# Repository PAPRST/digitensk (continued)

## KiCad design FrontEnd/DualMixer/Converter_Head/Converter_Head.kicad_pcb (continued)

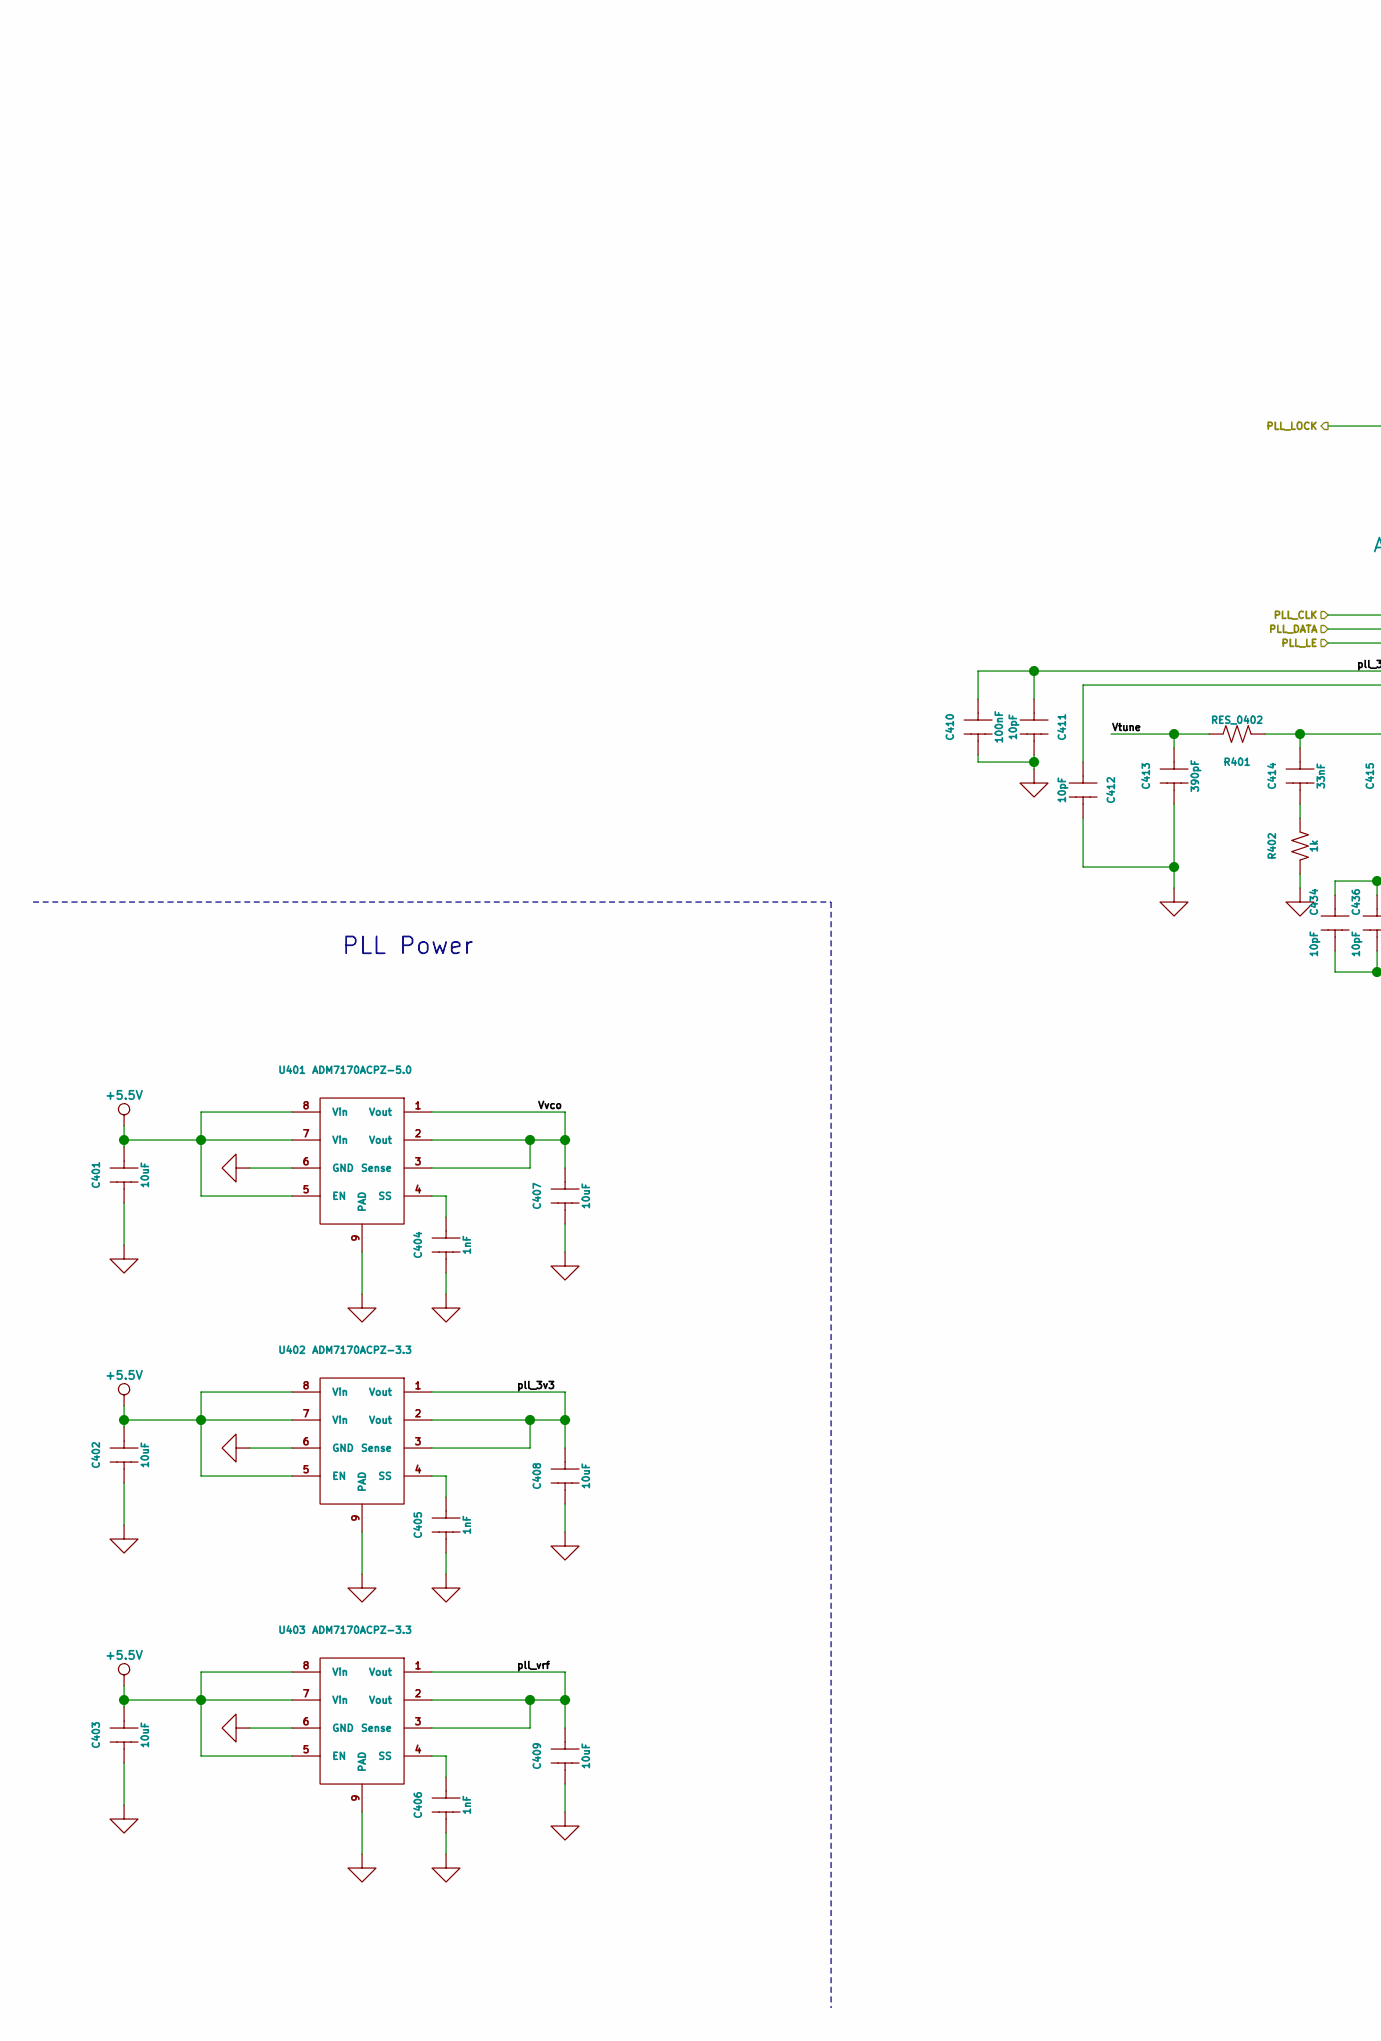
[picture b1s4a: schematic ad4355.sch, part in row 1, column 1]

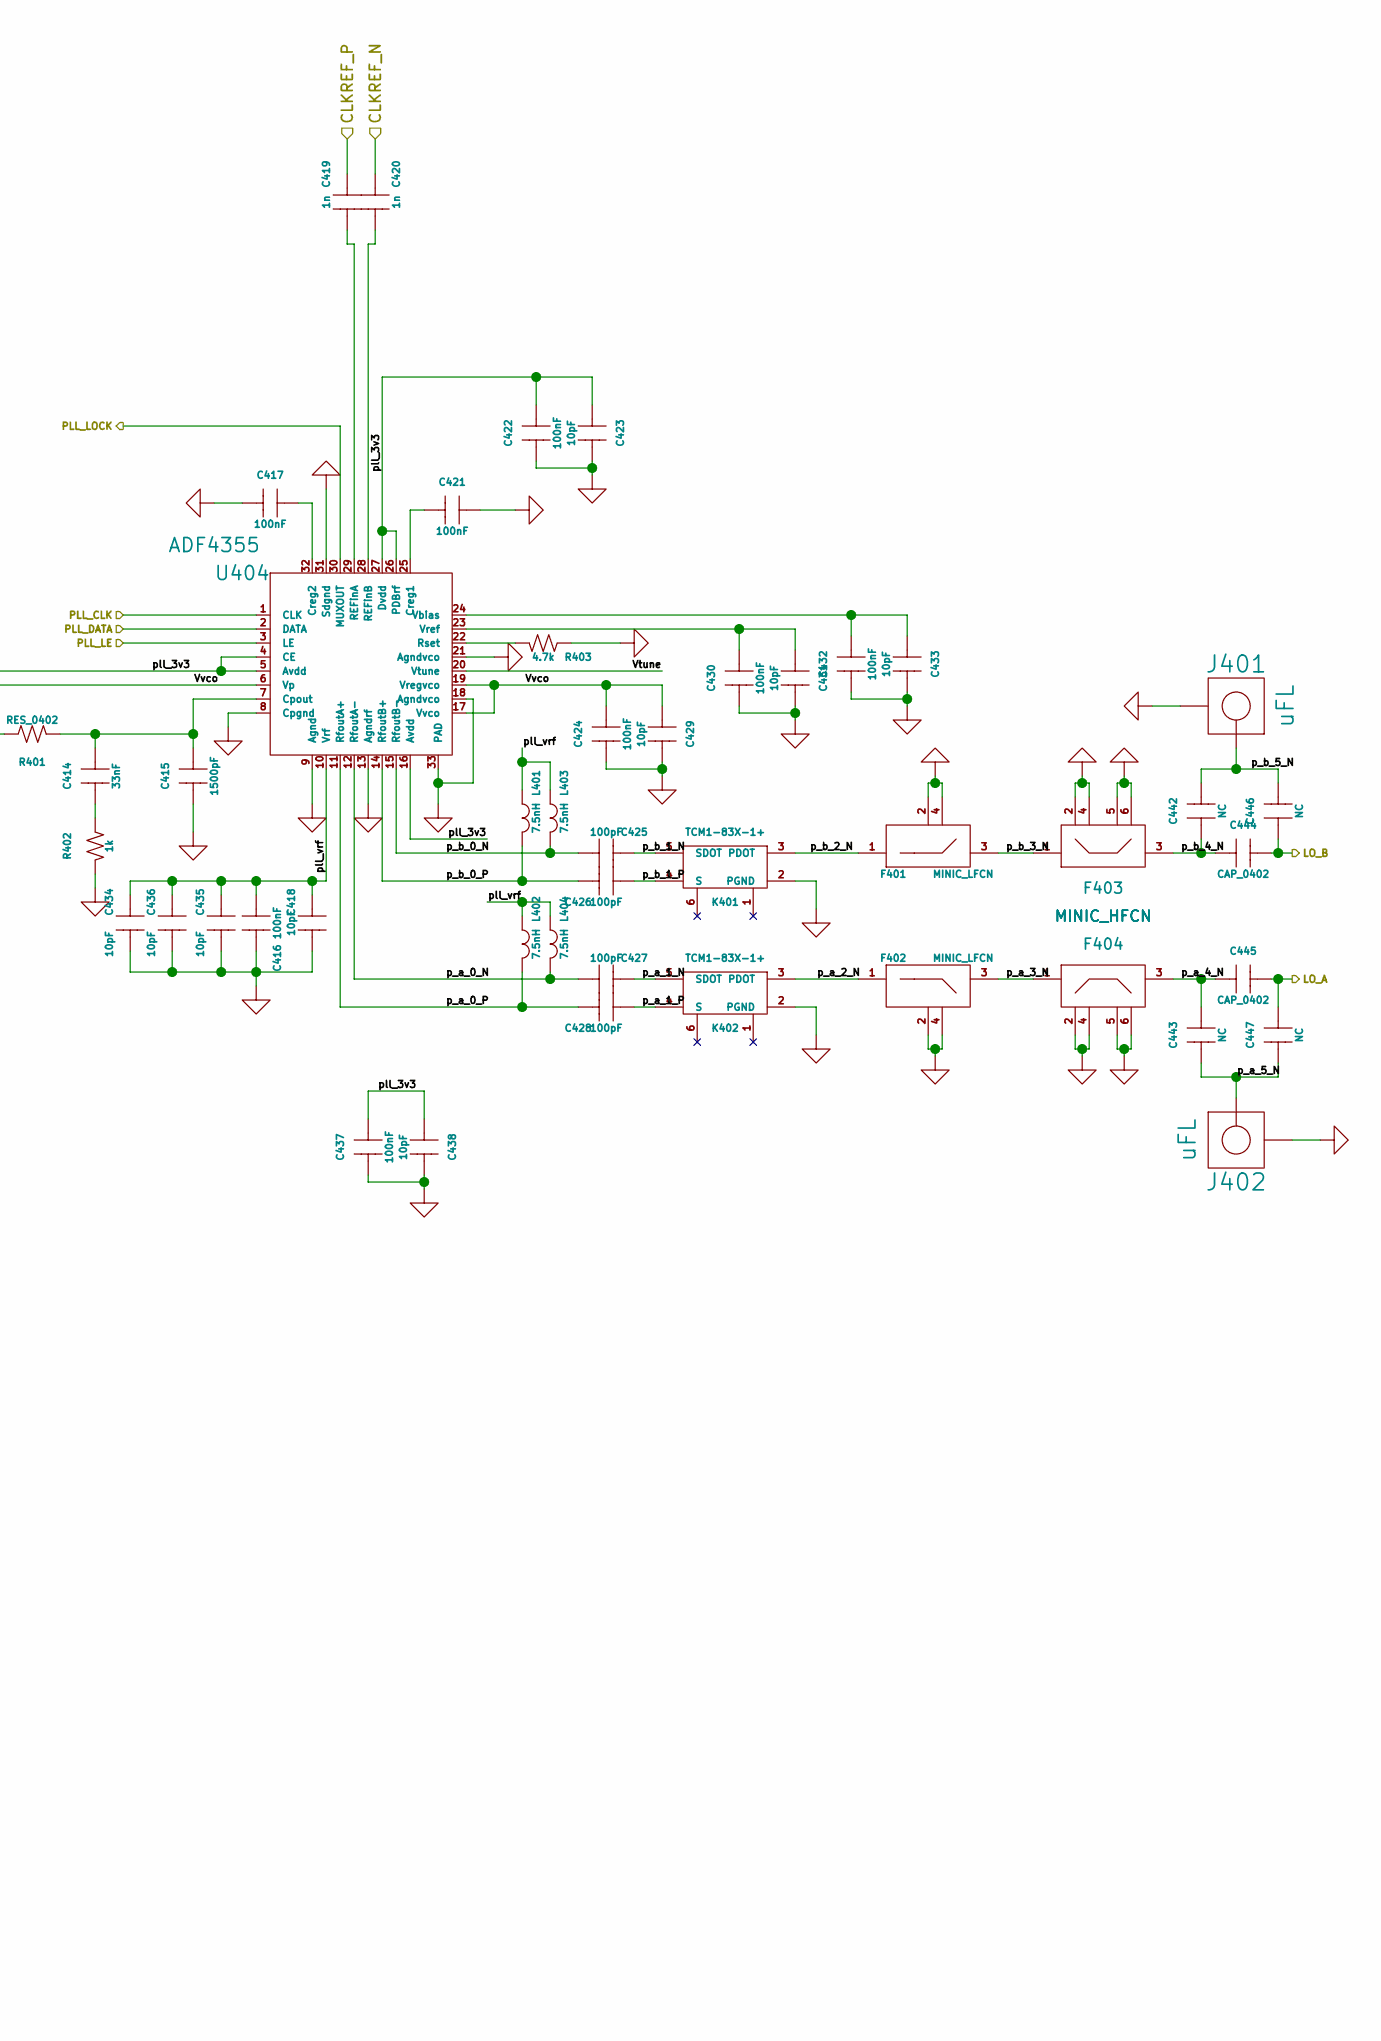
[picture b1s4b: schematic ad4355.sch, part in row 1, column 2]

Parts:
C401, C402, C403, C407, C408, C409: 10uF; SM0805
C404, C405, C406: 1nF; SM0603
C410, C416, C417, C421, C422, C424, C430, C432, C437: 100nF; SM0402
C411, C412, C418, C423, C429, C431, C433, C434, C435, C436, C438: 10pF; SM0402
C413: 390pF; SM0402
C414: 33nF; SM0402
C415: 1500pF; SM0402
C419, C420: 1n; SM0402
C425, C426, C427, C428: 100pF; SM0402
C442, C443, C446, C447: NC; SM0402
C444, C445: CAP_0402; SM0402
F401, F402: MINIC_LFCN; FV1206
F403, F404: MINIC_HFCN; FV1206
J401, J402: uFL; U.FL-R-SMT-1
K401, K402: TCM1-83X-1+; DB1627
L401, L402, L403, L404: 7.5nH; SM0402
R401: RES_0402; SM0402
R402: 1k; SM0402
R403: 4.7k; SM0402
U401: ADM7170ACPZ-5.0; DFN8_3x3mm
U402, U403: ADM7170ACPZ-3.3; DFN8_3x3mm
U404: ADF4355; QFN32_5x5mm_3.6mm

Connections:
+5.5V: C401.1, C402.1, C403.1, U401.5 (EN), U401.7 (Vin), U401.8 (Vin), U402.5 (EN), U402.7 (Vin), U402.8 (Vin), U403.5 (EN), U403.7 (Vin), U403.8 (Vin); also elsewhere on the board
/ADF4355 PLL/CLKREF_N: C420.1; also elsewhere on the board
/ADF4355 PLL/CLKREF_P: C419.1; also elsewhere on the board
/ADF4355 PLL/LO_A: C445.2, C447.1; also elsewhere on the board
/ADF4355 PLL/LO_B: C444.2, C446.1; also elsewhere on the board
/ADF4355 PLL/Vtune: C413.1, R401.1, U404.20 (Vtune)
/ADF4355 PLL/Vvco: C407.1, C412.1, C424.1, C429.1, U401.1 (Vout), U401.2 (Vout), U401.3 (Sense), U404.6 (Vp), U404.17 (Vvco), U404.19 (Vregvco)
/ADF4355 PLL/p_a_0_N: C427.1, L404.2, U404.12 (RfoutA-)
/ADF4355 PLL/p_a_0_P: C428.2, L402.2, U404.11 (RfoutA+)
/ADF4355 PLL/p_a_1_N: C427.2, K402.5 (SDOT)
/ADF4355 PLL/p_a_1_P: C428.1, K402.4 (S)
/ADF4355 PLL/p_a_2_N: F402.1 (RFIN), K402.3 (PDOT)
/ADF4355 PLL/p_a_3_N: F402.3 (RFOUT), F404.1 (RFIN)
/ADF4355 PLL/p_a_4_N: C443.1, C445.1, F404.3 (RFOUT)
/ADF4355 PLL/p_a_5_N: C443.2, C447.2, J402.1 (RF)
/ADF4355 PLL/p_b_0_N: C425.1, L403.2, U404.15 (RfoutB-)
/ADF4355 PLL/p_b_0_P: C426.2, L401.2, U404.14 (RfoutB+)
/ADF4355 PLL/p_b_1_N: C425.2, K401.5 (SDOT)
/ADF4355 PLL/p_b_1_P: C426.1, K401.4 (S)
/ADF4355 PLL/p_b_2_N: F401.1 (RFIN), K401.3 (PDOT)
/ADF4355 PLL/p_b_3_N: F401.3 (RFOUT), F403.1 (RFIN)
/ADF4355 PLL/p_b_4_N: C442.1, C444.1, F403.3 (RFOUT)
/ADF4355 PLL/p_b_5_N: C442.2, C446.2, J401.1 (RF)
/ADF4355 PLL/pll_3v3: C408.1, C410.1, C411.1, C422.1, C423.1, C437.1, C438.1, U402.1 (Vout), U402.2 (Vout), U402.3 (Sense), U404.4 (CE), U404.5 (Avdd), U404.16 (Avdd), U404.26 (PDBrf), U404.27 (Dvdd)
/ADF4355 PLL/pll_vrf: C409.1, C416.1, C418.1, C434.1, C435.1, C436.1, L401.1, L402.1, L403.1, L404.1, U403.1 (Vout), U403.2 (Vout), U403.3 (Sense), U404.10 (Vrf)
/MOSI: U404.2 (DATA); also elsewhere on the board
/PLL_LOCK: U404.30 (MUXOUT); also elsewhere on the board
/SCK: U404.1 (CLK); also elsewhere on the board
/~PLL_CS: U404.3 (LE); also elsewhere on the board
GND: C401.2, C402.2, C403.2, C404.2, C405.2, C406.2, C407.2, C408.2, C409.2, C410.2, C411.2, C412.2, C413.2, C415.2, C416.2, C417.2, C418.2, C421.1, C422.2, C423.2, C424.2, C429.2, C430.2, C431.2, C432.2, C433.2, C434.2, C435.2, C436.2, C437.2, C438.2, F401.2 (GND), F401.4 (GND), F402.2 (GND), F402.4 (GND), F403.2 (GND), F403.4 (GND), F403.5 (GND), F403.6 (GND), F404.2 (GND), F404.4 (GND), F404.5 (GND), F404.6 (GND), J401.2 (GND), J402.2 (GND), K401.2 (PGND), K402.2 (PGND), R402.2, R403.1, U401.6 (GND), U401.9 (PAD), U402.6 (GND), U402.9 (PAD), U403.6 (GND), U403.9 (PAD), U404.8 (Cpgnd), U404.9 (Agnd), U404.13 (Agndrf), U404.18 (Agndvco), U404.21 (Agndvco), U404.31 (Sdgnd), U404.33 (PAD); also elsewhere on the board
unnamed: C404.1, U401.4 (SS)
unnamed: C405.1, U402.4 (SS)
unnamed: C406.1, U403.4 (SS)
unnamed: C414.1, C415.1, R401.2, U404.7 (Cpout)
unnamed: C414.2, R402.1
unnamed: C417.1, U404.32 (Creg2)
unnamed: C419.2, U404.29 (REFinA)
unnamed: C420.2, U404.28 (REFinB)
unnamed: C421.2, U404.25 (Creg1)
unnamed: C430.1, C431.1, U404.23 (Vref)
unnamed: C432.1, C433.1, U404.24 (Vbias)
unnamed: R403.2, U404.22 (Rset)

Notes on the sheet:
PLL Power

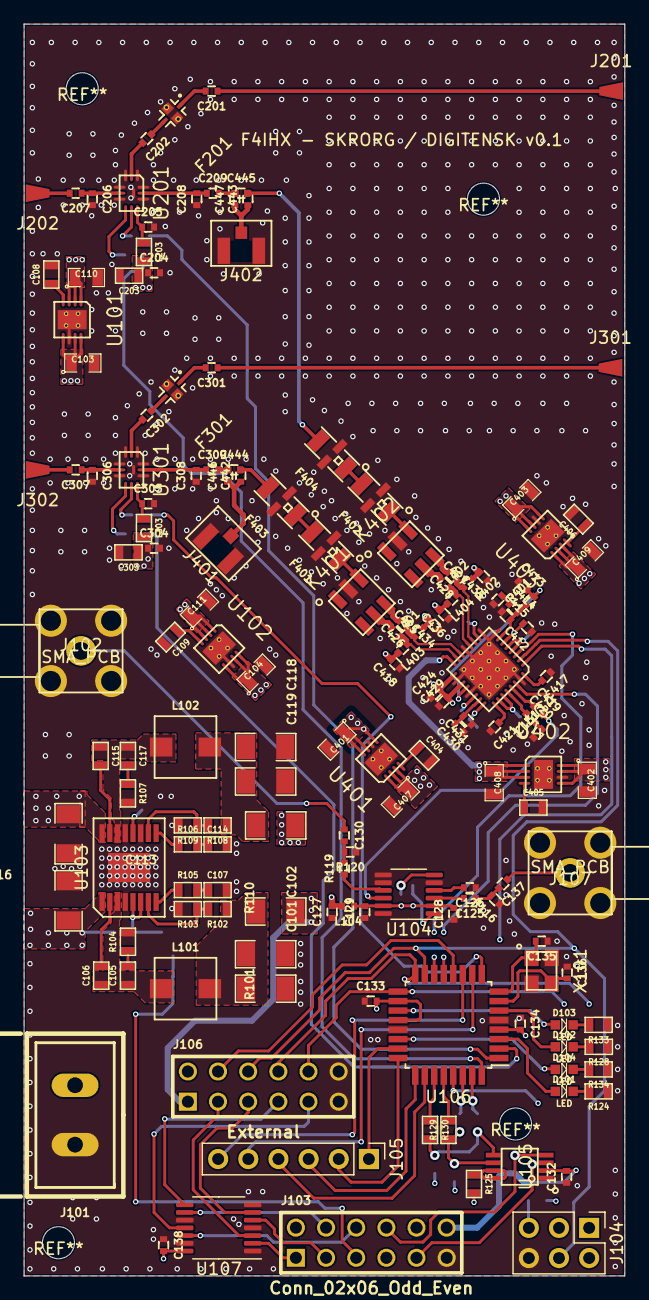
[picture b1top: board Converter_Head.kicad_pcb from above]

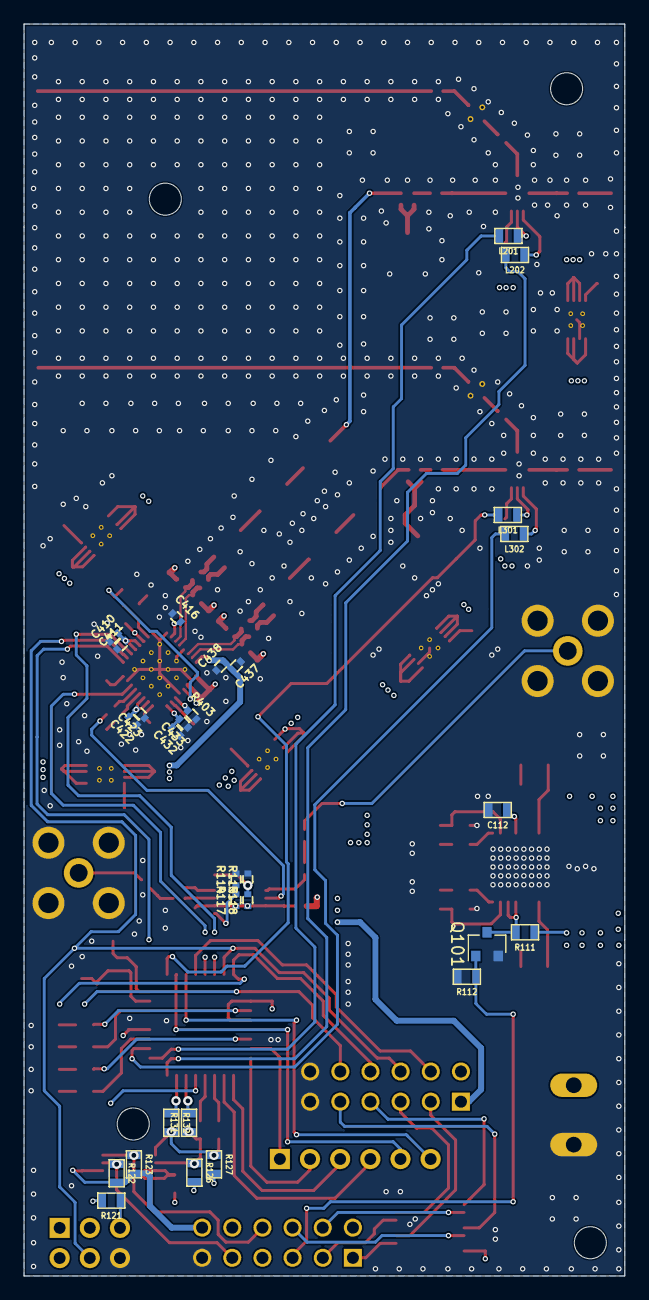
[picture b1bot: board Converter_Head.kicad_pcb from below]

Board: 4 copper layers, 50.6 x 105.5 mm, 184 parts (29 on the bottom side), 136 nets.

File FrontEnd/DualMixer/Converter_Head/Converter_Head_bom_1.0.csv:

Component,Part,References,Value,Vendor,SKU,Footprint,Quantity Per PCB,Man. Ref.,Status
1,CAP_0402,C206 C208 C306 C308,0.15pF,,,SM0402,4,,
2,CAP_0402,C125 C127 C128 C129 C130 C131 C132 C133 C134 C137 C138,0.1uF,,,SM0402,11,,
3,CAP_0603,C114,1.68n,,,SM0603,1,,
4,CAP_0603,C410 C416 C417 C421 C422 C424 C430 C432 C437,100nF,,,SM0402,9,,
5,CAP_0402,C425 C426 C427 C428,100pF,,,SM0402,4,,
6,CAP_0402,C126,10nF,,,SM0402,1,,
7,CAP_0402,C135 C136 C411 C412 C418 C423 C429 C431 C433 C434 C435 C436 C438,10pF,,,SM0402,13,,
8,CAP_1206,C101 C102 C113 C116 C118 C119,10u,,,SM1206,6,,
9,CAP_0805,C103 C104 C110 C111 C401 C402 C403 C407 C408 C409,10uF,,,SM0805,10,,
10,CAP_0402,C415,1500pF,,,SM0402,1,,
11,CAP_0402,C419 C420,1n,,,SM0402,2,,
12,CAP_0603,C108 C109 C404 C405 C406,1nF,,,SM0603,5,,
13,CAP_0603,C203 C303,1uF,,,SM0603,2,,
14,CAP_0603,C107,2.8n,,,SM0603,1,,
15,CAP_0402,C205 C207 C209 C305 C307 C309,22pF,,,SM0402,6,,
16,CAP_0402,C201 C202 C301 C302,30pF,,,SM0402,4,,
17,CAP_0402,C414,33nF,,,SM0402,1,,
18,CAP_0402,C413,390pF,,,SM0402,1,,
19,CAP_0603,C112,4.7u,,,SM0603,1,,
20,CAP_0603,C105 C117,470p,,,SM0603,2,,
21,CAP_0603,C106 C115,47n,,,SM0603,2,,
22,CAP_0402,C204 C304,47pF,,,SM0402,2,,
23,CAP_0402,C444 C445,CAP_0402,,,SM0402,2,,
24,CAP_0402,C442 C443 C446 C447,NC,,,SM0402,4,,
25,LED,D101 D102 D103 D104,LED,,,LED-0603,4,,
26,BFCW,F201 F301,BFCW-542+,,,JC0603C,2,,
27,MINIC_HFCN,F403 F404,MINIC_HFCN,,,FV1206,2,,
28,MINIC_LFCN,F401 F402,MINIC_LFCN,,,FV1206,2,,
29,Conn_01x03,J101,Conn_01x03,,,MOL_CONN_2_VH,1,,
30,Conn_01x06,J105,Conn_01x06,,,PinHeader_1x06_P2.54mm_Vertical,1,,
31,Conn_02x03_Odd_Even,J104,Conn_02x03_Odd_Even,,,PinHeader_2x03_P2.54mm_Vertical,1,,
32,Conn_02x06_Odd_Even,J103 J106,Conn_02x06_Odd_Even,,,pin_array_6x2,2,,
33,SMA_PCB,J102 J107,SMA_PCB,,,SMA_RA_PCB_Amphenol,2,,
34,SMA_PCB,J201 J202 J301 J302,SMA_PCB,,,PAD_T_200x110um,4,,
35,uFL,J401 J402,uFL,,,U.FL-R-SMT-1,2,,
36,TCM1-83X-1+,K401 K402,TCM1-83X-1+,,,DB1627,2,,
37,IND_SMALL,L101 L102,5.6uH,,,WE-HCI_SMD_5.6x5.3x4,2,744316560,
38,IND_0402,L401 L402 L403 L404,7.5nH,,,SM0402,4,,
39,IND_0402,L104,IND_0402,,,SM0402,1,,
40,IND_0603,L201 L202 L203 L301 L302 L303,IND_0603,,,SM0603,6,,
41,BSS138,Q101,BSS138,,,SOT-23,1,,
42,RES_1206,R101 R110,0,,,SM1206,2,,
43,RES_0402,R117 R118 R119,0,,,SM0402,3,,
44,RES_0603,R129 R130 R131 R132,0,,,SM0603,4,,
45,RES_0603,R104 R107,10,,,SM0603,2,,
46,RES_0603,R124 R128 R133 R134,100,,,SM0603,4,,
47,RES_0603,R111 R112 R121 R122 R123 R126 R127,10k,,,SM0603,7,,
48,RES_0402,R402,1k,,,SM0402,1,,
49,RES_0603,R102 R108,20.5k,,,SM0603,2,,
50,RES_0603,R125,2000k,,,SM0603,1,,
51,RES_0603,R103,3.48k,,,SM0603,1,,
52,RES_0603,R105,34.8k,,,SM0603,1,,
53,RES_0402,R403,4.7k,,,SM0402,1,,
54,RES_0402,R116,50,,,SM0402,1,,
55,RES_0603,R106,57.6k,,,SM0603,1,,
56,RES_0603,R109,6.49k,,,SM0603,1,,
57,RES_0402,R114 R115 R120,NC,,,SM0402,3,,
58,RES_0402,R401,RES_0402,,,SM0402,1,,
59,ADF4355,U404,ADF4355,,,QFN32_5x5mm_3.6mm,1,,OK
60,ADM7170,U101 U102 U402 U403,ADM7170ACPZ-3.3,MOUSER,584-ADM7170ACPZ3.3R7,DFN8_3x3mm,4,,
61,ADM7170,U401,ADM7170ACPZ-5.0,MOUSER,584-ADM7170ACPZ5.0R7,DFN8_3x3mm,1,,
62,ATmega328PB-AU,U106,ATmega328PB-AU,MOUSER,556-ATMEGA328PB-AU ,TQFP-32_7x7mm_P0.8mm,1,,
63,LTC5549,U201 U301,LTC5549,,,QFN12_2x3mm_UDB_LT,2,,
64,LTC6957IMS-3,U104,LTC6957IMS-3,MOUSER,584-LTC6957IMS-3#PBF,MSOP-12_3x4mm_P0.65mm,1,,
65,PCA9306DCT_SSOP,U105,PCA9306DCT_SSOP,,,SSOP8,1,,
66,SN74LV4T125,U107,SN74LV4T125,,,TSSOP-14_4.4x5mm_P0.65mm,1,,
67,TPS5429x,U103,TPS54292,,,PowerPad_TSSOP_16,1,,
68,SMD_XTAL_small,X101,8MHz,,,xtal_3.2x2.5,1,,
,,,,,,,,,
,,,,,,,,,
,,,,,,,,,
,,,,,,,,,
,,,,,,,,,
Component Groups:,68,,,,,,,,
Component Count:,184,,,,,,,,
Fitted Components:,184,,,,,,,,
Number of PCBs:,1,,,,,,,,
Total components:,184,,,,,,,,
Schematic Version:,1.0,,,,,,,,
Schematic Date:,2020-10-04,,,,,,,,
PCB Variant:,[u'default'],,,,,,,,
BoM Date:,lun. 14 juin 2021 23:31:11,,,,,,,,
Schematic Source:,/home/nats/data/projects/digitensk/FrontEnd/DualMixer/Converter_Head/Converter_Head.sch,,,,,,,,
KiCad Version:,Eeschema 5.1.9-73d0e3b20d~88~ubuntu18.04.1,,,,,,,,

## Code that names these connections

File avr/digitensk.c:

#include <avr/io.h>
#include <util/delay.h>
#include <string.h>

#include "main.h"

// Fuse
// L: 0xE2 H: 0xDA E: 0xF8
// Freq_osc: 16MHz
// Freq_cpu: 8MHz
// avrdude -c avrispmkii -p m328pb -U lfuse:w:0xe2:m -U hfuse:w:0xda:m -U efuse:w:0xf8:m
// avr-gcc -Os -DF_CPU=8000000UL -mmcu=atmega328pb -c -o digitensk.o digitensk.c
// avr-gcc -mmcu=atmega328pb digitensk.o -o digitensk
// avr-objcopy -O ihex -R .eeprom digitensk digitensk.hex
// avrdude -c avrispmkii -p m328pb -U flash:w:digitensk.hex:i

void init_io() {

	// PORTB
	// PB0 : External CS
	// PB1 : PLL Lock Indicator
	// PB2 - PB5 : SPI PLL chip
	// PB6 - PB7 : XTAL Osc
	PORTB = 0x0;
	PORTB |= _BV(PB0);
	PORTB |= _BV(PB2);
	DDRB |= _BV(PB0);
	DDRB |= _BV(PB2);
	DDRB |= _BV(PB3);
	DDRB |= _BV(PB5);

	// PORTC
	// PC0 - PC4 : Input frequency selector
	// PC5 : Output Disable RF PSU
	// PC6 : RESET Input
	PORTC = 0x0;

	// PORTD
	// PD0 - PD1 : UART
	// PD2 : Mixer 1 Enable
	// PD3 : Mixer 1 Doubler
	// PD4 : Mixer 2 Enable
	// PD5 : Mixer 2 Doubler
	PORTD = 0x0;
	DDRD |= _BV(PD2);
	DDRD |= _BV(PD3);
	DDRD |= _BV(PD4);
	DDRD |= _BV(PD5);

	// PORTD
	// PE0 : LED1
	// PE1 : LED2
	// PE2 : LED3
	// PE3 : LED4
	PORTE = 0x0;
	DDRE |= _BV(PE0);
	DDRE |= _BV(PE1);
	DDRE |= _BV(PE2);
	DDRE |= _BV(PE3);
}

void init_uart() {
	// UBRRn = Fosc / (16* baud) - 1
	// Baud = 38400
	UBRR0H = 0x00;
	UBRR0L = 0x0C;

	UCSR0B |= (1 << TXEN0);
}

void init_spi() {
	SPCR0 = (1 << SPE) | (1 << MSTR);
}

void activate_uart_rx(uint8_t activate) {
	if( !activate )
		UCSR0B &= ~(1 << RXEN0);
	else
		UCSR0B |= (1 << RXEN0);
}

// Send one char to uart
void uart_putc(char data) {
    while(!(UCSR0A & (1 << UDRE0)));
    UDR0 = data;
}

// Read one char to uart
uint8_t uart_readc(uint8_t * val) {
	if(UCSR0A & (1<<RXC0)) {
		*val = UDR0;
		return 1;
	}
	return 0;
}

// Sending a string over uart (no safety !)
void send_str(char sText[]) {
	uint8_t len = strlen(sText);
	for(uint8_t i = 0; i < len; i++) {
		uart_putc(sText[i]);
	}
}

// Get PLL Lock
uint8_t get_lock() {
	if ((PINB & (1 << PB1))) {
		return 1;
	}
	return 0;
}

// SPI Writing register
void write_reg(uint32_t data){
	// ~CS
	PORTB &= ~_BV(PB2);
	PORTB &= ~_BV(PB0);

	_delay_ms(1);

	SPDR0 = (uint8_t)((data >> 24) & 0xFF);

	while(!(SPSR0 & (1 << SPIF)));

	SPDR0 = (uint8_t)((data >> 16) & 0xFF);

	while(!(SPSR0 & (1 << SPIF)));

	SPDR0 = (data >> 8) & 0xFF;

	while(!(SPSR0 & (1 << SPIF)));

	SPDR0 = (data) & 0xFF;

	while(!(SPSR0 & (1 << SPIF)));

	_delay_ms(1);

	PORTB |= _BV(PB2);
	PORTB |= _BV(PB0);
}

// Drive LEDS
void led_status(uint8_t leds) {
	PORTE = 0x0F & leds;
}

// Drive MIXER
void mixer_status(uint8_t mixers) {
	PORTD = PORTD | (((mixers << 2) & 0x3C));
}

// Set PLL parameters
void set_freq(Freq_Set set, uint8_t first) {
	if(first == 1) {
		write_reg(set.reg12);
		_delay_ms(10);
		write_reg(set.reg11);
		_delay_ms(10);
		write_reg(set.reg10);
		_delay_ms(10);
		write_reg(set.reg9);
		_delay_ms(10);
		write_reg(set.reg8);
		_delay_ms(10);
		write_reg(set.reg7);
		_delay_ms(10);
		write_reg(set.reg6);
		_delay_ms(10);
		write_reg(set.reg5);
		_delay_ms(10);
		write_reg(set.reg4);
		_delay_ms(10);
		write_reg(set.reg3);
		_delay_ms(10);
		write_reg(set.reg2);
		_delay_ms(10);
		write_reg(set.reg1);
		_delay_ms(150);
		write_reg(set.reg0);
	} else {

	}
}

int main() {
	init_io();
	init_uart();
	init_spi();

	//mixer_status(0xC0);

	PORTD = 0x14;

	set_freq(set_array[0], 1);

	while (1) {
		led_status(14 + get_lock());
	}
}

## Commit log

2020-10-04 Init of project
2020-10-04 starting layout
2020-10-05 Added power, needs to add communication connector
2021-06-06 sent in production
2021-07-17 writing avr code
2021-07-31 starting work on modulation
2021-08-08 working TRX
2021-09-10 kazami
